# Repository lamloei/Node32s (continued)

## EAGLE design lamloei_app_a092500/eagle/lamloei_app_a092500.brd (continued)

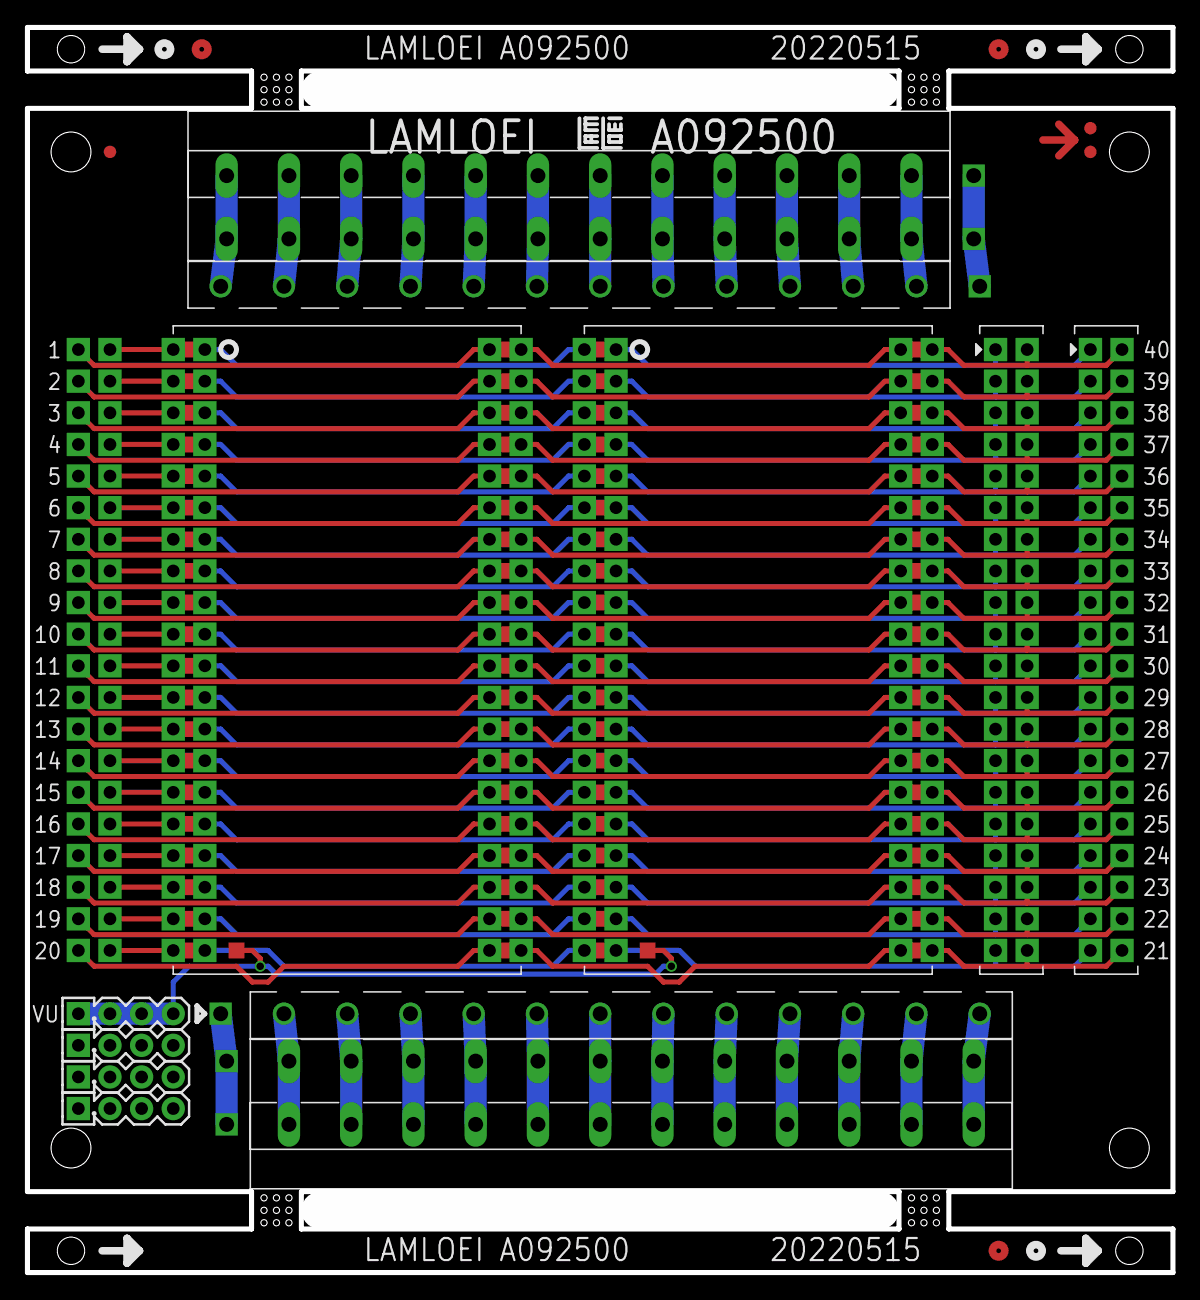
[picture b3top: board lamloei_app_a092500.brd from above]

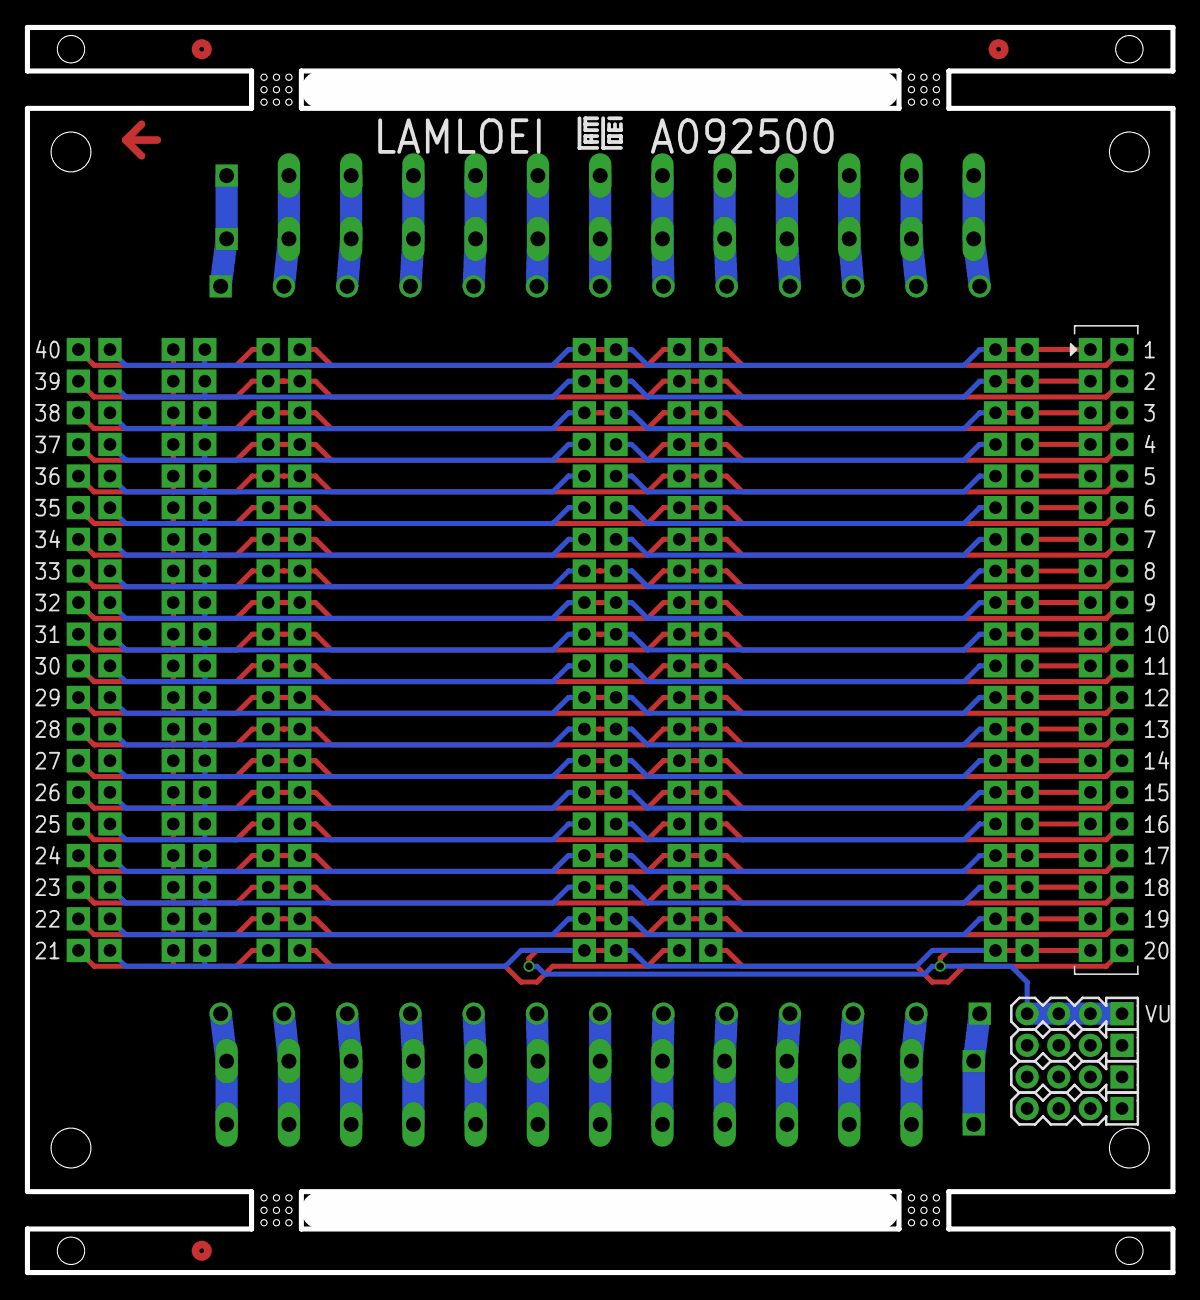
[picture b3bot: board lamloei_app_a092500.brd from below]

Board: 2 copper layers, 89.4 x 97.4 mm, 20 parts (2 on the bottom side), 67 nets.

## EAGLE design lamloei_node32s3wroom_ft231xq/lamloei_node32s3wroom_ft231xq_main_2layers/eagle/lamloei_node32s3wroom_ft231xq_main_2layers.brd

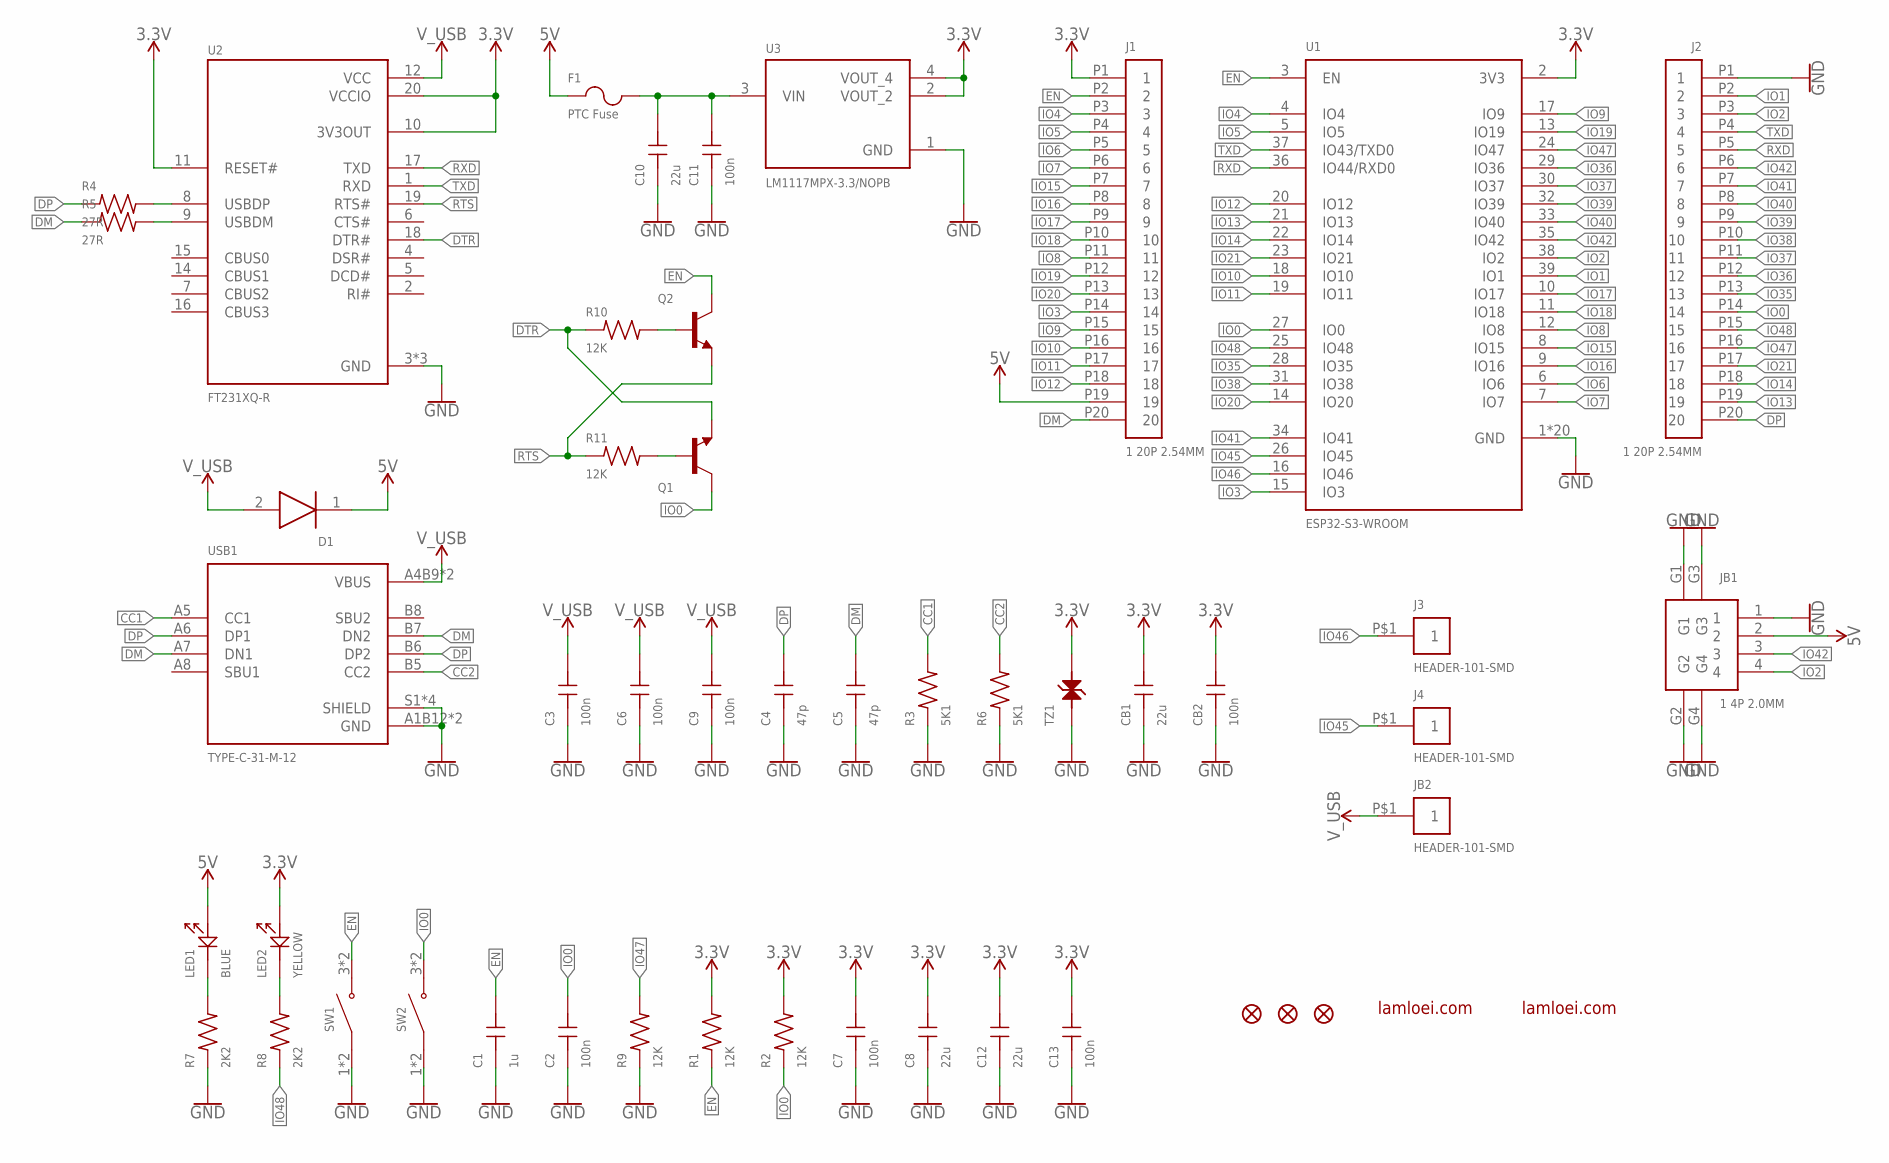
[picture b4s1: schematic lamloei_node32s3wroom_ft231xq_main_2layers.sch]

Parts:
C1: 1u; GRM155R70J105KA12D
C2, C3, C6, C7, C9, C11, C13: 100n; GCM155R71H104KE02D
C4, C5: 47p; GCM1555C1H470JA16D
C8, C10, C12: 22u; GCM21BR71H105KA03L
CB1: 22u; GCM21BR71H105KA03L
CB2: 100n; GCM155R71H104KE02D
D1: PMEG4050EP,115
F1: PTC Fuse; MF-NSMF050-2
J1, J2: 1 20P 2.54MM; HEADER-120
J3, J4: HEADER-101-SMD
JB1: 1 4P 2.0MM; A2012WR-S-4P
JB2: HEADER-101-SMD
LED1: BLUE; 19-217BHC-ZL1M2RY3T
LED2: YELLOW; 19-213/Y2C-CQ2R2L/3T(CY)
Q1, Q2: BC847B,215
R1, R2, R9, R10, R11: 12K; R0402
R3, R6: 5K1; R0402
R4, R5: 27R; R0402
R7, R8: 2K2; R0402
SW1, SW2: K2-1808SN-A4SW-01
TZ1: LXES15AAA1-153
U1: ESP32-S3-WROOM
U2: FT231XQ-R
U3: LM1117MPX-3.3/NOPB
USB1: TYPE-C-31-M-12
ZFD1, ZFD2, ZFD3: FIDUCIAL1X2; FIDUCIAL-1X2
ZL1, ZL2: LAMLEOI_LOGO_3

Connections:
3.3V: C7.2, C8.2, C12.2, C13.2, CB1.2, CB2.2, J1.P1 (1), LED2.2, R1.2, R2.2, TZ1.2, U1.2 (3V3), U2.10 (3V3OUT), U2.11 (RESET#), U2.20 (VCCIO), U3.2 (VOUT_2), U3.4 (VOUT_4)
5V: D1.1 (K), F1.1, J1.P19 (19), JB1.2, LED1.2
CC1: R3.2, USB1.A5 (CC1)
CC2: R6.2, USB1.B5 (CC2)
DM: C5.2, J1.P20 (20), R5.1, USB1.A7 (DN1), USB1.B7 (DN2)
DP: C4.2, J2.P20 (20), R4.1, USB1.A6 (DP1), USB1.B6 (DP2)
DTR: Q1.E, R10.1, U2.18 (DTR#)
EN: C1.2, J1.P2 (2), Q2.C, R1.1, SW1.3 (NO), SW1.4 (NO), U1.3 (EN)
GND: C1.1, C2.1, C3.1, C4.1, C5.1, C6.1, C7.1, C8.1, C9.1, C10.1, C11.1, C12.1, C13.1, CB1.1, CB2.1, J2.P1 (1), JB1.1, JB1.G1, JB1.G2, JB1.G3, JB1.G4, R3.1, R6.1, R7.1, R9.1, SW1.1 (COM), SW1.2 (COM), SW2.1 (COM), SW2.2 (COM), TZ1.1, U1.1 (GND), U1.1.1 (GND), U1.1.2 (GND), U1.1.3 (GND), U1.1.4 (GND), U1.1.5 (GND), U1.1.6 (GND), U1.1.7 (GND), U1.1.8 (GND), U1.1.9 (GND), U1.1.10 (GND), U1.1.11 (GND), U1.1.12 (GND), U1.1.13 (GND), U1.1.14 (GND), U1.1.15 (GND), U1.1.16 (GND), U1.1.17 (GND), U1.1.18 (GND), U1.40 (GND), U2.3 (GND), U2.13 (GND), U2.21 (GND), U3.1 (GND), USB1.A1B12 (GND), USB1.B1A12 (GND), USB1.S1 (SHIELD), USB1.S2 (SHIELD), USB1.S3 (SHIELD), USB1.S4 (SHIELD)
IO0: C2.2, J2.P14 (14), Q1.C, R2.1, SW2.3 (NO), SW2.4 (NO), U1.27 (IO0)
IO1: J2.P2 (2), U1.39 (IO1)
IO2: J2.P3 (3), JB1.4, U1.38 (IO2)
IO3: J1.P14 (14), U1.15 (IO3)
IO4: J1.P3 (3), U1.4 (IO4)
IO5: J1.P4 (4), U1.5 (IO5)
IO6: J1.P5 (5), U1.6 (IO6)
IO7: J1.P6 (6), U1.7 (IO7)
IO8: J1.P11 (11), U1.12 (IO8)
IO9: J1.P15 (15), U1.17 (IO9)
IO10: J1.P16 (16), U1.18 (IO10)
IO11: J1.P17 (17), U1.19 (IO11)
IO12: J1.P18 (18), U1.20 (IO12)
IO13: J2.P19 (19), U1.21 (IO13)
IO14: J2.P18 (18), U1.22 (IO14)
IO15: J1.P7 (7), U1.8 (IO15)
IO16: J1.P8 (8), U1.9 (IO16)
IO17: J1.P9 (9), U1.10 (IO17)
IO18: J1.P10 (10), U1.11 (IO18)
IO19: J1.P12 (12), U1.13 (IO19)
IO20: J1.P13 (13), U1.14 (IO20)
IO21: J2.P17 (17), U1.23 (IO21)
IO35: J2.P13 (13), U1.28 (IO35)
IO36: J2.P12 (12), U1.29 (IO36)
IO37: J2.P11 (11), U1.30 (IO37)
IO38: J2.P10 (10), U1.31 (IO38)
IO39: J2.P9 (9), U1.32 (IO39)
IO40: J2.P8 (8), U1.33 (IO40)
IO41: J2.P7 (7), U1.34 (IO41)
IO42: J2.P6 (6), JB1.3, U1.35 (IO42)
IO45: J4.P$1, U1.26 (IO45)
IO46: J3.P$1, U1.16 (IO46)
IO47: J2.P16 (16), R9.2, U1.24 (IO47)
IO48: J2.P15 (15), R8.1, U1.25 (IO48)
unnamed: R4.2, U2.8 (USBDP)
unnamed: R5.2, U2.9 (USBDM)
unnamed: C10.2, C11.2, F1.2, U3.3 (VIN)
unnamed: LED1.1, R7.2
unnamed: LED2.1, R8.2
unnamed: Q2.B, R10.2
unnamed: Q1.B, R11.2
RTS: Q2.E, R11.1, U2.19 (RTS#)
RXD: J2.P5 (5), U1.36 (IO44/RXD0), U2.17 (TXD)
TXD: J2.P4 (4), U1.37 (IO43/TXD0), U2.1 (RXD)
V_USB: C3.2, C6.2, C9.2, D1.2 (A), JB2.P$1, U2.12 (VCC), USB1.A4B9 (VBUS), USB1.B4A9 (VBUS)

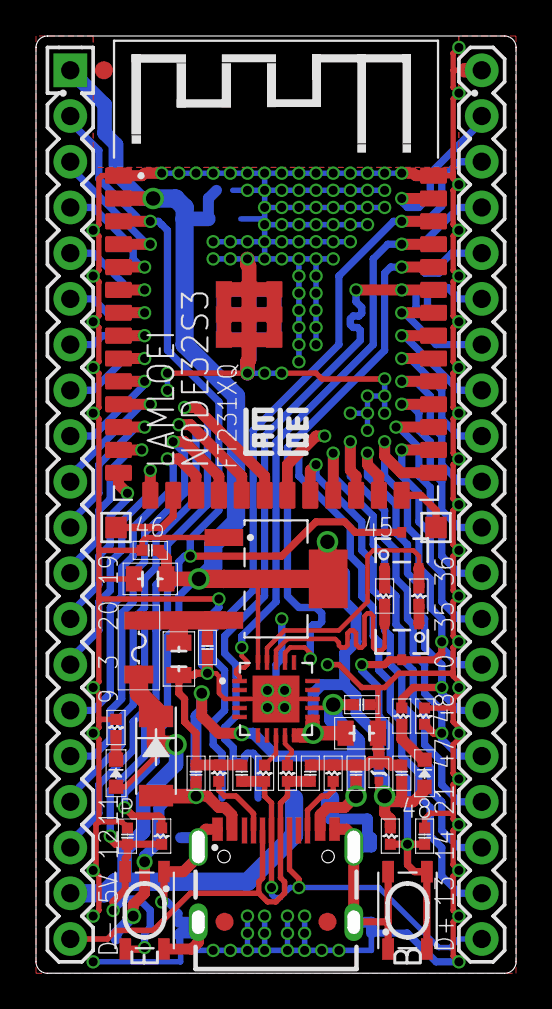
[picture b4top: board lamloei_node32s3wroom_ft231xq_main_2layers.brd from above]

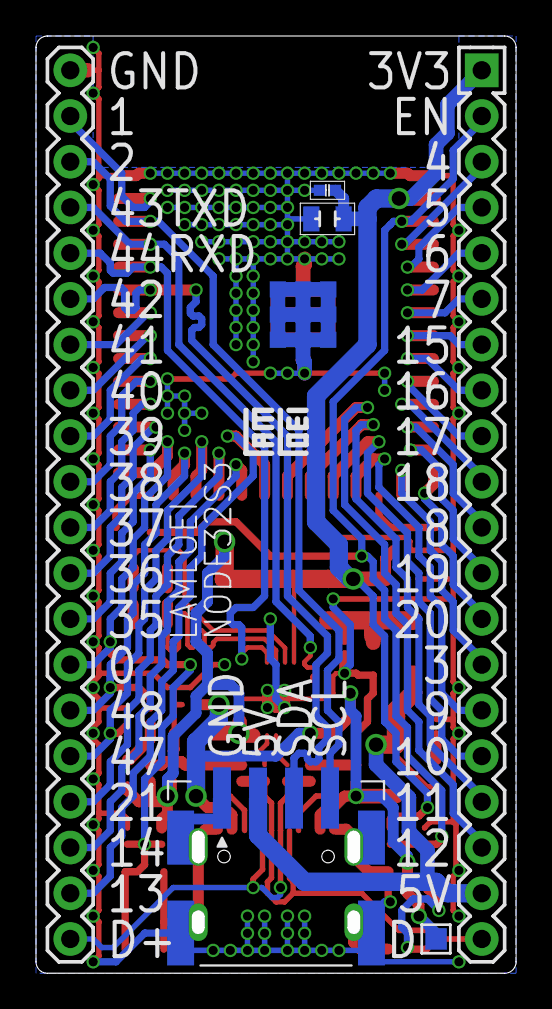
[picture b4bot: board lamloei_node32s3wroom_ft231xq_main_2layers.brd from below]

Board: 2 copper layers, 26.0 x 51.4 mm, 50 parts (5 on the bottom side), 54 nets.

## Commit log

2022-04-24 lamloei_node32s3wroom_cp2102
    lamloei_node32s3wroom_cp2102
2022-04-24 lamloei_node32s3wroom_cp2102
2022-04-30 lamloei_breadout_a09201
2022-05-04 lamloei_node32s3wroom_ft231xq
2022-05-07 lamloei_node32s3wroom_cp2102_main_4layers
2022-05-07 lamloei_node32s3wroom_cp2102_msmd_2layers
2022-05-10 lamloei_node32s3wroom_cp2102_10_4layers
2022-05-10 lamloei_node32s3wroom_cp2102_msmd_4layers
2022-05-10 lamloei_node32s3wroom_cp2102_10_2layers
2022-05-10 lamloei_node32s3wroom_cp2102_main_2layers
2022-05-10 lamloei_node32s3wroom_cp2102_smf_4layers
2022-05-16 lamloei_breadout_a07201
2022-05-17 lamloei_app_a092500
2022-05-25 lamloei_logo
2022-06-18 lamloei node32s3wroom cp2102
2022-06-25 node32s
